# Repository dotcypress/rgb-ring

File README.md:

# RGB Ring

Rust powered RGB light ring.

## Resources

- [Firmware(WIP)](firmware/)
- [PCB(KiCad project)](pcb/)
- [Gerber files](docs/fabrication.zip)
- [Schematics](docs/rgb-ring-schematics.pdf)

## License

Licensed under either of

- Apache License, Version 2.0 ([LICENSE-APACHE](LICENSE-APACHE) or
  http://www.apache.org/licenses/LICENSE-2.0)
- MIT license ([LICENSE-MIT](LICENSE-MIT) or http://opensource.org/licenses/MIT)

at your option.

### Contribution

Unless you explicitly state otherwise, any contribution intentionally submitted
for inclusion in the work by you, as defined in the Apache-2.0 license, shall be
dual licensed as above, without any additional terms or conditions.

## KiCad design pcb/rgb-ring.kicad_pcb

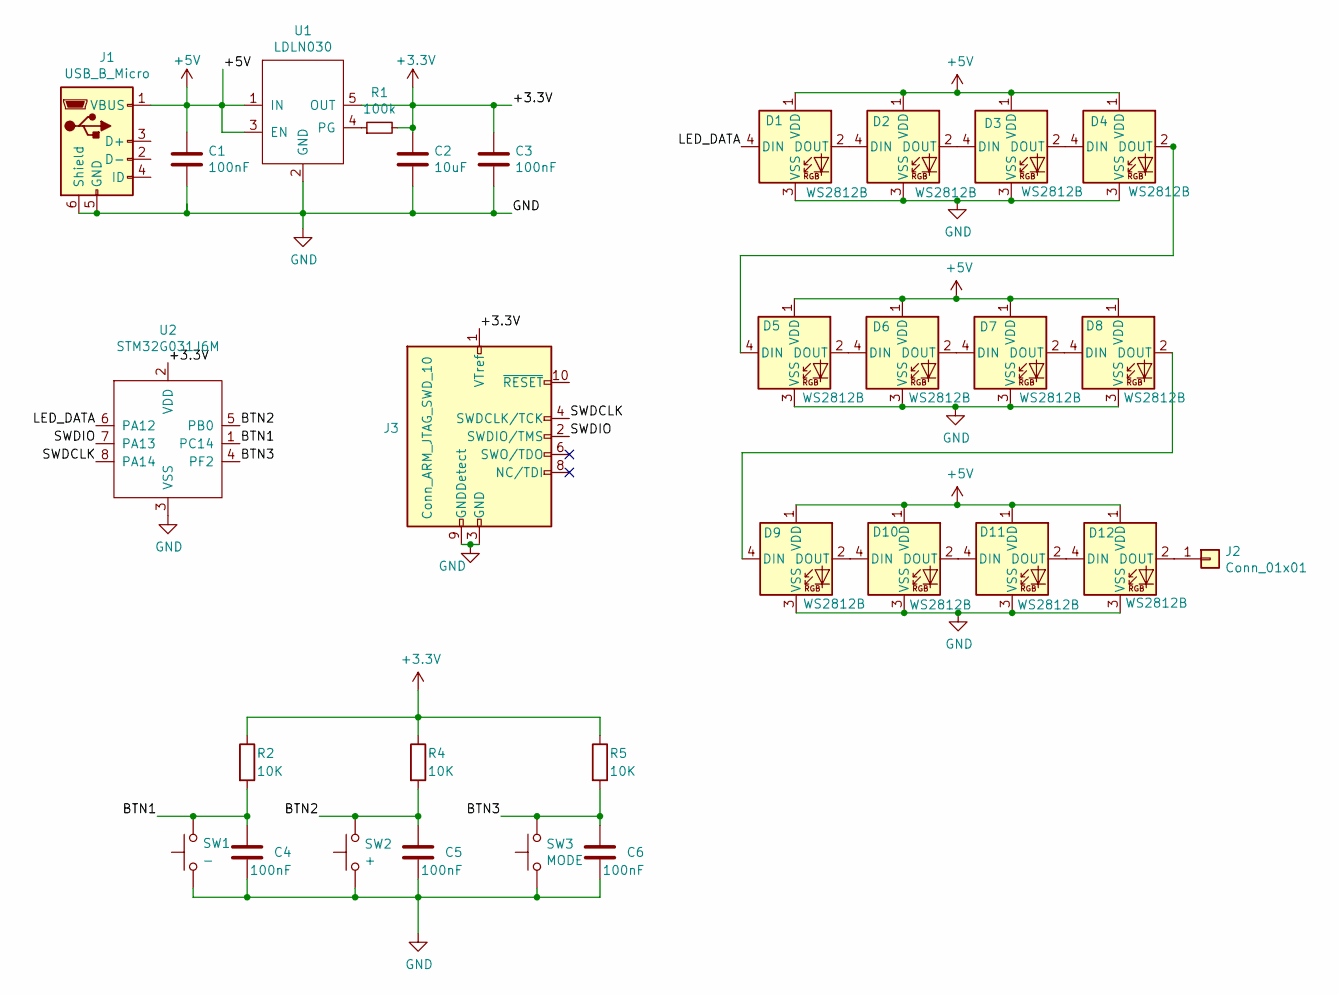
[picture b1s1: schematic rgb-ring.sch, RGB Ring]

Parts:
C1, C3, C4, C5, C6: 100nF; C_0603_1608Metric
C2: 10uF; C_0603_1608Metric
D1, D2, D3, D4, D5, D6, D7, D8, D9, D10, D11, D12: WS2812B; LED_WS2812B_PLCC4_5.0x5.0mm_P3.2mm
J1: USB_B_Micro; USB_Micro-B_Amphenol_10103594-0001LF_Horizontal
J2: Conn_01x01; PinHeader_1x01_P1.00mm_Vertical
J3: Conn_ARM_JTAG_SWD_10; PinHeader_2x05_P1.27mm_Vertical_SMD
R1: 100k; R_0603_1608Metric
R2, R4, R5: 10K; R_0603_1608Metric
SW1: -; SW_SPST_CK_RS282G05A3
SW2: +; SW_SPST_CK_RS282G05A3
SW3: MODE; SW_SPST_CK_RS282G05A3
U1: LDLN030; TSOT-23-5
U2: STM32G031J6M; SO-8_3.9x4.9mm_P1.27mm

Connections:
+3V3: C2.1, C3.1, J3.1 (VTref), R1.2, R2.1, R4.1, R5.1, U1.5 (OUT), U2.2 (VDD)
+5V: C1.1, D1.1 (VDD), D2.1 (VDD), D3.1 (VDD), D4.1 (VDD), D5.1 (VDD), D6.1 (VDD), D7.1 (VDD), D8.1 (VDD), D9.1 (VDD), D10.1 (VDD), D11.1 (VDD), D12.1 (VDD), J1.1 (VBUS), U1.1 (IN), U1.3 (EN)
/BTN1: C4.2, R2.2, SW1.2, U2.1 (PC14)
/BTN2: C5.2, R4.2, SW2.2, U2.5 (PB0)
/BTN3: C6.2, R5.2, SW3.2, U2.4 (PF2)
/LED_DATA: D1.4 (DIN), U2.6 (PA12)
/SWDCLK: J3.4 (SWDCLK/TCK), U2.8 (PA14)
/SWDIO: J3.2 (SWDIO/TMS), U2.7 (PA13)
GND: C1.2, C2.2, C3.2, C4.1, C5.1, C6.1, D1.3 (VSS), D2.3 (VSS), D3.3 (VSS), D4.3 (VSS), D5.3 (VSS), D6.3 (VSS), D7.3 (VSS), D8.3 (VSS), D9.3 (VSS), D10.3 (VSS), D11.3 (VSS), D12.3 (VSS), J1.5 (GND), J1.6 (Shield), J3.3 (GND), J3.5 (GND), J3.9 (GNDDetect), SW1.1, SW2.1, SW3.1, U1.2 (GND), U2.3 (VSS)
unnamed: D1.2 (DOUT), D2.4 (DIN)
unnamed: D2.2 (DOUT), D3.4 (DIN)
unnamed: D3.2 (DOUT), D4.4 (DIN)
unnamed: D4.2 (DOUT), D5.4 (DIN)
unnamed: D5.2 (DOUT), D6.4 (DIN)
unnamed: D6.2 (DOUT), D7.4 (DIN)
unnamed: D7.2 (DOUT), D8.4 (DIN)
unnamed: D8.2 (DOUT), D9.4 (DIN)
unnamed: D10.2 (DOUT), D11.4 (DIN)
unnamed: D9.2 (DOUT), D10.4 (DIN)
unnamed: D11.2 (DOUT), D12.4 (DIN)
unnamed: D12.2 (DOUT), J2.1
unnamed: R1.1, U1.4 (PG)

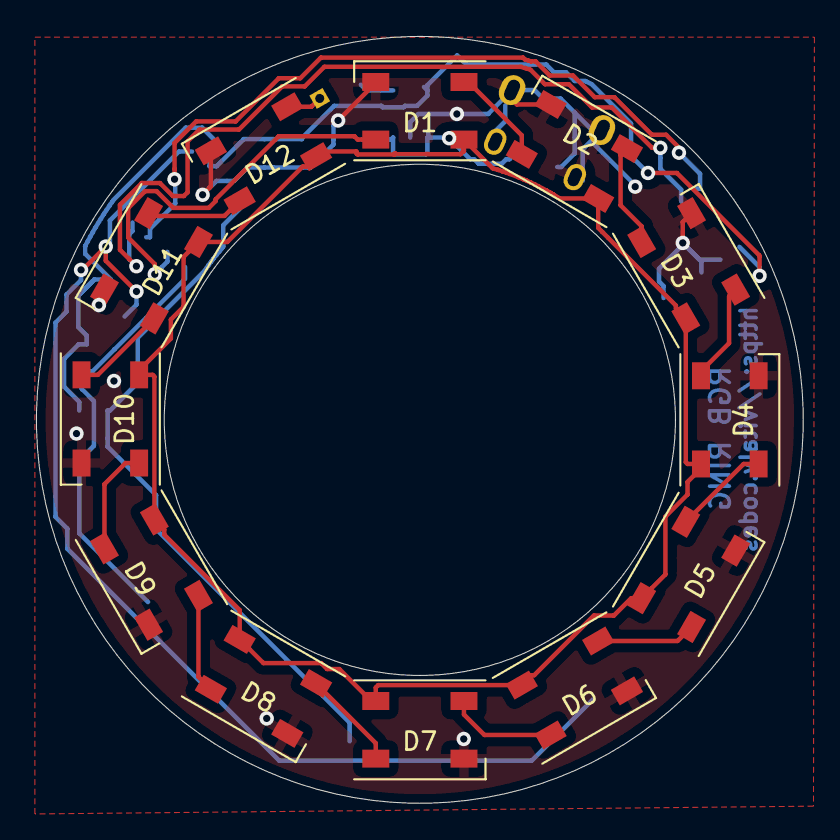
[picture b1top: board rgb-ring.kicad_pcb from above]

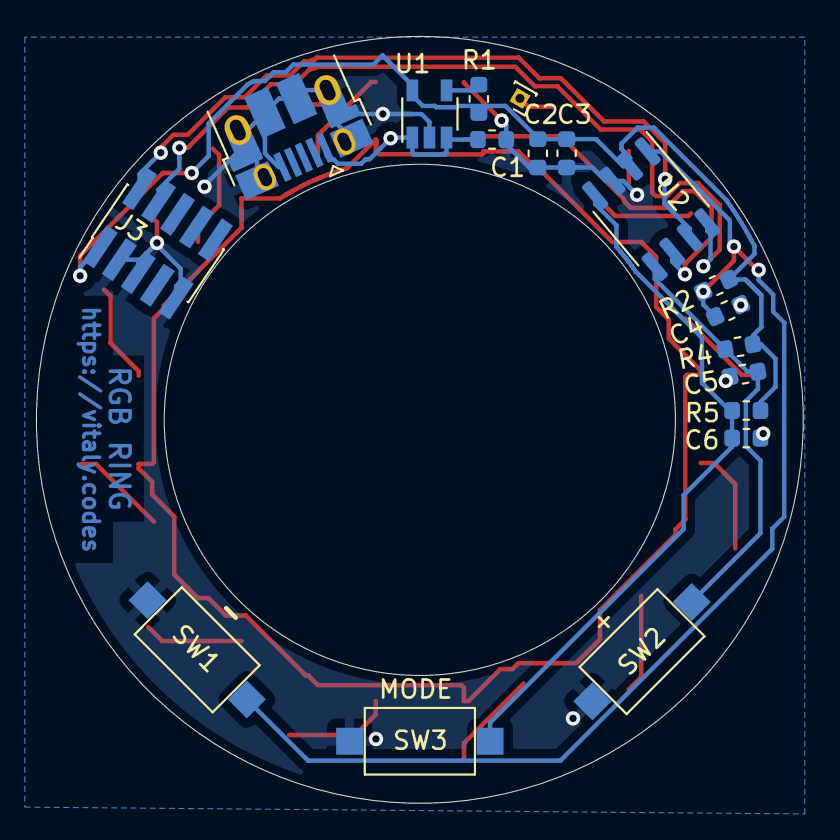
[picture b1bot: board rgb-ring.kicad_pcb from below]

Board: 2 copper layers, 42.6 x 42.6 mm, 30 parts (18 on the bottom side), 22 nets.

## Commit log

2020-01-11 fixes
2020-01-11 refactoring
2020-01-12 add palette
2020-04-11 tuning
